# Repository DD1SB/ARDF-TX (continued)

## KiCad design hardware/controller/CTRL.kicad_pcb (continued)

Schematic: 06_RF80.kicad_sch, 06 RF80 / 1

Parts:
C40, C42, C43: 100n; C_0603_1608Metric_CTL; MPN CL10B104KB8NNNC
C41: 1u; C_0603_1608Metric_CTL; MPN CL10A105KB8NNNC
J4: RF80 keyed controller link; IDC16_61201621621; MPN 61201621621
R80, R101, R103, R105, R107: 10k; R_0603_1608Metric_CTL; MPN RC0603FR-0710KL
R100, R102, R104, R106, R108: 100; R_0603_1608Metric_CTL; MPN RC0603FR-07100RL
U40: TPS22918DBVR; SOT-23-6_CTL; MPN TPS22918DBVR
U41: SN74LVC244APWR; TSSOP-20_4.4x6.5mm_P0.65mm_CTL; MPN SN74LVC244APWR
U42: SN74LVC125APWR; TSSOP-14_4.4x5mm_P0.65mm_CTL; MPN SN74LVC125APWR

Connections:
ARM: U41.2 (2_A); also elsewhere on the board
FOX_REQ: U41.13 (13_A); also elsewhere on the board
GND: C40.2, C41.2, C42.2, C43.2, J4.2 (2_IO), J4.4 (4_IO), J4.16 (16_IO), R101.2, R103.2, R105.2, R107.2, U40.2 (2_GND), U41.10 (10_GND), U42.5 (5_A), U42.7 (7_GND), U42.9 (9_A), U42.12 (12_A); also elsewhere on the board
KEY: U41.4 (4_A); also elsewhere on the board
MUTE_RELEASE: U41.8 (8_A); also elsewhere on the board
OE80_N: R80.2, U41.1 (1_OE1_N), U41.19 (19_OE2_N), U42.1 (1_OE_N); also elsewhere on the board
PACK4_SOFT: U42.2 (2_A); also elsewhere on the board
PA_REQ: U41.11 (11_A); also elsewhere on the board
POWER80: U40.3 (3_ON); also elsewhere on the board
PROGRESS: U41.6 (6_A); also elsewhere on the board
PWR0: U41.15 (15_A); also elsewhere on the board
PWR1: U41.17 (17_A); also elsewhere on the board
RF80_ARM: J4.7 (7_IO), R100.2, R101.1
RF80_ARM_BUF: R100.1, U41.18 (18_Y)
RF80_CW_KEY: J4.8 (8_IO), R102.2, R103.1
RF80_CW_KEY_BUF: R102.1, U41.16 (16_Y)
RF80_FAULT_N: J4.14 (14_IO); also elsewhere on the board
RF80_FOX_REQ: J4.10 (10_IO); also elsewhere on the board
RF80_FOX_REQ_BUF: U41.7 (7_Y); also elsewhere on the board
RF80_LEASE: J4.6 (6_IO), R104.2, R105.1
RF80_LEASE_BUF: R104.1, U41.14 (14_Y)
RF80_MUTE_N: J4.13 (13_IO), R106.2, R107.1
RF80_MUTE_N_BUF: R106.1, U41.12 (12_Y)
RF80_PACK4_OK: J4.15 (15_IO); also elsewhere on the board
RF80_PACK4_OK_BUF: U42.3 (3_Y); also elsewhere on the board
RF80_PA_REQ: J4.9 (9_IO), R108.2; also elsewhere on the board
RF80_PA_REQ_BUF: R108.1, U41.9 (9_Y)
RF80_PWR0: J4.11 (11_IO); also elsewhere on the board
RF80_PWR0_BUF: U41.5 (5_Y); also elsewhere on the board
RF80_PWR1: J4.12 (12_IO); also elsewhere on the board
RF80_PWR1_BUF: U41.3 (3_Y); also elsewhere on the board
RF80_SCL: J4.3 (3_IO); also elsewhere on the board
RF80_SDA: J4.5 (5_IO); also elsewhere on the board
V3V3: U40.1 (1_IN); also elsewhere on the board
V3V3_RF80: C40.1, C41.1, C42.1, C43.1, J4.1 (1_IO), R80.1, U40.5 (5_QOD), U40.6 (6_OUT), U41.20 (20_VCC), U42.4 (4_OE_N), U42.10 (10_OE_N), U42.13 (13_OE_N), U42.14 (14_VCC); also elsewhere on the board

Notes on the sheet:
06 RF80 / 1
M6-C1R1 candidate: REVIEW / ALL hardware measurements NOT RUN / no ordering or manufacture.

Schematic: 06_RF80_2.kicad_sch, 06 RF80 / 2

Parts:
C44, C45: 100n; C_0603_1608Metric_CTL; MPN CL10B104KB8NNNC
R81: 2.2k; R_0603_1608Metric_CTL; MPN RC0603FR-072K2L
R109, R111, R113, R115, R117: 10k; R_0603_1608Metric_CTL; MPN RC0603FR-0710KL
R110, R112, R114, R116: 100; R_0603_1608Metric_CTL; MPN RC0603FR-07100RL
U43: TCA9517DR; SOIC-8_3.9x4.9mm_P1.27mm_CTL; MPN TCA9517DR

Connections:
BUS80_EN: U43.5 (5_EN); also elsewhere on the board
GND: C44.2, C45.2, R109.2, R111.2, R113.2, R115.2, R117.2, U43.4 (4_GND); also elsewhere on the board
RF80_FAULT_N: R81.1; also elsewhere on the board
RF80_FOX_REQ: R110.2, R111.1; also elsewhere on the board
RF80_FOX_REQ_BUF: R110.1; also elsewhere on the board
RF80_PACK4_OK: R116.2, R117.1; also elsewhere on the board
RF80_PACK4_OK_BUF: R116.1; also elsewhere on the board
RF80_PA_REQ: R109.1; also elsewhere on the board
RF80_PWR0: R112.2, R113.1; also elsewhere on the board
RF80_PWR0_BUF: R112.1; also elsewhere on the board
RF80_PWR1: R114.2, R115.1; also elsewhere on the board
RF80_PWR1_BUF: R114.1; also elsewhere on the board
RF80_SCL: U43.7 (7_SCLB); also elsewhere on the board
RF80_SDA: U43.6 (6_SDAB); also elsewhere on the board
RTC80_SCL: U43.2 (2_SCLA); also elsewhere on the board
RTC80_SDA: U43.3 (3_SDAA); also elsewhere on the board
V3V3: C45.1, U43.1 (1_VCCA); also elsewhere on the board
V3V3_RF80: C44.1, R81.2, U43.8 (8_VCCB); also elsewhere on the board

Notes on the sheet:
06 RF80 / 2
M6-C1R1 candidate: REVIEW / ALL hardware measurements NOT RUN / no ordering or manufacture.

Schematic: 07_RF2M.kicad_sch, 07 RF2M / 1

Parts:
C50, C52, C53: 100n; C_0603_1608Metric_CTL; MPN CL10B104KB8NNNC
C51: 1u; C_0603_1608Metric_CTL; MPN CL10A105KB8NNNC
J5: RF2M keyed controller link; IDC20_61202021621; MPN 61202021621
R90, R119, R121, R123, R125: 10k; R_0603_1608Metric_CTL; MPN RC0603FR-0710KL
R118, R120, R122, R124, R126: 100; R_0603_1608Metric_CTL; MPN RC0603FR-07100RL
U50: TPS22918DBVR; SOT-23-6_CTL; MPN TPS22918DBVR
U51: SN74LVC244APWR; TSSOP-20_4.4x6.5mm_P0.65mm_CTL; MPN SN74LVC244APWR
U52: SN74LVC125APWR; TSSOP-14_4.4x5mm_P0.65mm_CTL; MPN SN74LVC125APWR

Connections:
AF_PWM: U51.17 (17_A); also elsewhere on the board
ARM: U51.2 (2_A); also elsewhere on the board
GND: C50.2, C51.2, C52.2, C53.2, J5.2 (2_IO), J5.17 (17_IO), J5.18 (18_IO), R119.2, R121.2, R123.2, R125.2, U50.2 (2_GND), U51.10 (10_GND), U52.7 (7_GND), U52.12 (12_A); also elsewhere on the board
KEY: U51.6 (6_A); also elsewhere on the board
LEVEL_PWM: U52.2 (2_A); also elsewhere on the board
MUTE_RELEASE: U51.11 (11_A); also elsewhere on the board
OE2M_N: R90.2, U51.1 (1_OE1_N), U51.19 (19_OE2_N), U52.1 (1_OE_N), U52.4 (4_OE_N), U52.10 (10_OE_N); also elsewhere on the board
PATH_TRAIN: U51.13 (13_A); also elsewhere on the board
PA_PREPARE: U52.9 (9_A); also elsewhere on the board
POWER2M: U50.3 (3_ON); also elsewhere on the board
PREPARE: U52.5 (5_A); also elsewhere on the board
PROFILE_FULL: U51.15 (15_A); also elsewhere on the board
PROGRESS: U51.8 (8_A); also elsewhere on the board
RF2M_AF_PWM: J5.13 (13_IO); also elsewhere on the board
RF2M_AF_PWM_BUF: U51.3 (3_Y); also elsewhere on the board
RF2M_ARM: J5.5 (5_IO), R118.2, R119.1
RF2M_ARM_BUF: R118.1, U51.18 (18_Y)
RF2M_FAULT_N: J5.16 (16_IO); also elsewhere on the board
RF2M_I2C_SCL: J5.4 (4_IO); also elsewhere on the board
RF2M_I2C_SDA: J5.3 (3_IO); also elsewhere on the board
RF2M_KEY: J5.7 (7_IO), R122.2, R123.1
RF2M_KEY_BUF: R122.1, U51.14 (14_Y)
RF2M_LEVEL_PWM: J5.14 (14_IO); also elsewhere on the board
RF2M_LEVEL_PWM_BUF: U52.3 (3_Y); also elsewhere on the board
RF2M_MODULE_ID: J5.19 (19_IO); also elsewhere on the board
RF2M_MUTE_N: J5.9 (9_IO), R126.2; also elsewhere on the board
RF2M_MUTE_N_BUF: R126.1, U51.9 (9_Y)
RF2M_PATH_TRAIN: J5.11 (11_IO); also elsewhere on the board
RF2M_PATH_TRAIN_BUF: U51.7 (7_Y); also elsewhere on the board
RF2M_PA_PREPARE: J5.20 (20_IO); also elsewhere on the board
RF2M_PA_PREPARE_BUF: U52.8 (8_Y); also elsewhere on the board
RF2M_PA_RAIL_ADC: J5.10 (10_IO); also elsewhere on the board
RF2M_PREPARE: J5.15 (15_IO); also elsewhere on the board
RF2M_PREPARE_BUF: U52.6 (6_Y); also elsewhere on the board
RF2M_PROFILE_FULL: J5.12 (12_IO); also elsewhere on the board
RF2M_PROFILE_FULL_BUF: U51.5 (5_Y); also elsewhere on the board
RF2M_PROGRESS: J5.8 (8_IO), R124.2, R125.1
RF2M_PROGRESS_BUF: R124.1, U51.12 (12_Y)
RF2M_SLOT: J5.6 (6_IO), R120.2, R121.1
RF2M_SLOT_BUF: R120.1, U51.16 (16_Y)
SLOT: U51.4 (4_A); also elsewhere on the board
V3V3: U50.1 (1_IN); also elsewhere on the board
V3V3_RF2M: C50.1, C51.1, C52.1, C53.1, J5.1 (1_IO), R90.1, U50.5 (5_QOD), U50.6 (6_OUT), U51.20 (20_VCC), U52.13 (13_OE_N), U52.14 (14_VCC); also elsewhere on the board

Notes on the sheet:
07 RF2M / 1
M6-C1R1 candidate: REVIEW / ALL hardware measurements NOT RUN / no ordering or manufacture.

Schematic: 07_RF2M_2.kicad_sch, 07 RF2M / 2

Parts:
C54, C55: 100n; C_0603_1608Metric_CTL; MPN CL10B104KB8NNNC
R91, R127, R129, R131, R133, R135, R137, R139: 10k; R_0603_1608Metric_CTL; MPN RC0603FR-0710KL
R128, R130, R132, R134, R136, R138: 100; R_0603_1608Metric_CTL; MPN RC0603FR-07100RL
U53: TCA9517DR; SOIC-8_3.9x4.9mm_P1.27mm_CTL; MPN TCA9517DR

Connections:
BUS2M_EN: U53.5 (5_EN); also elsewhere on the board
GND: C54.2, C55.2, R91.2, R127.2, R129.2, R131.2, R133.2, R135.2, R137.2, R139.2, U53.4 (4_GND); also elsewhere on the board
RF2M_AF_PWM: R132.2, R133.1; also elsewhere on the board
RF2M_AF_PWM_BUF: R132.1; also elsewhere on the board
RF2M_FAULT_N: R91.1; also elsewhere on the board
RF2M_I2C_SCL: U53.7 (7_SCLB); also elsewhere on the board
RF2M_I2C_SDA: U53.6 (6_SDAB); also elsewhere on the board
RF2M_LEVEL_PWM: R134.2, R135.1; also elsewhere on the board
RF2M_LEVEL_PWM_BUF: R134.1; also elsewhere on the board
RF2M_MUTE_N: R127.1; also elsewhere on the board
RF2M_PATH_TRAIN: R128.2, R129.1; also elsewhere on the board
RF2M_PATH_TRAIN_BUF: R128.1; also elsewhere on the board
RF2M_PA_PREPARE: R138.2, R139.1; also elsewhere on the board
RF2M_PA_PREPARE_BUF: R138.1; also elsewhere on the board
RF2M_PREPARE: R136.2, R137.1; also elsewhere on the board
RF2M_PREPARE_BUF: R136.1; also elsewhere on the board
RF2M_PROFILE_FULL: R130.2, R131.1; also elsewhere on the board
RF2M_PROFILE_FULL_BUF: R130.1; also elsewhere on the board
RF2M_SCL: U53.2 (2_SCLA); also elsewhere on the board
RF2M_SDA: U53.3 (3_SDAA); also elsewhere on the board
V3V3: C55.1, U53.1 (1_VCCA); also elsewhere on the board
V3V3_RF2M: C54.1, U53.8 (8_VCCB); also elsewhere on the board

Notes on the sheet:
07 RF2M / 2
M6-C1R1 candidate: REVIEW / ALL hardware measurements NOT RUN / no ordering or manufacture.

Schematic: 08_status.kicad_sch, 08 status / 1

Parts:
C60: 100n; C_0603_1608Metric_CTL; MPN CL10B104KB8NNNC
R93: 10k; R_0603_1608Metric_CTL; MPN RC0603FR-0710KL
U60: SN74LVC2G17DCKR; SOT-363_SC-70-6_CTL; MPN SN74LVC2G17DCKR

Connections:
GND: C60.2, R93.2, U60.3 (3_GND); also elsewhere on the board
RF2M_FAULT: U60.2 (2_2Y); also elsewhere on the board
RF2M_FAULT_N: U60.4 (4_2A); also elsewhere on the board
RF80_FAULT: U60.5 (5_1Y); also elsewhere on the board
RF80_FAULT_N: R93.1, U60.1 (1_1A); also elsewhere on the board
V3V3: C60.1, U60.6 (6_VCC); also elsewhere on the board

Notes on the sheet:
08 status / 1
M6-C1R1 candidate: REVIEW / ALL hardware measurements NOT RUN / no ordering or manufacture.

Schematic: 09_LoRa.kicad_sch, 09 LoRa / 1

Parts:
C70: 100n; C_0603_1608Metric_CTL; MPN CL10B104KB8NNNC; not fitted
C71: 10u 10V; C_0603_1608Metric_CTL; MPN CL10A106KP8NNNC; not fitted
J7: LoRa antenna U.FL; UFL_Standard; MPN U.FL-R-SMT-1(10); not fitted
R70, R71: 10k; R_0603_1608Metric_CTL; MPN RC0603FR-0710KL; not fitted
U70: Silicontra SX1262TR8-GC; Silicontra_SX1262ZTR8_GC; MPN SX1262TR8-GC; not fitted

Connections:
GND: C70.2, C71.2, J7.2 (2_IO), U70.1 (1_IO), U70.2 (2_IO), U70.3 (3_IO), U70.4 (4_IO), U70.11 (11_IO), U70.12 (12_IO), U70.19 (19_IO), U70.20 (20_IO), U70.22 (22_IO); also elsewhere on the board
LORA_ANT: J7.1 (1_IO), U70.21 (21_IO)
LORA_BUSY: U70.10 (10_BUSY); also elsewhere on the board
LORA_DIO1: U70.5 (5_DIO1); also elsewhere on the board
LORA_NSS: R70.2, U70.17 (17_NSS); also elsewhere on the board
LORA_RESET: R71.2, U70.18 (18_RST_N); also elsewhere on the board
SPI_MISO: U70.15 (15_MISO); also elsewhere on the board
SPI_MOSI: U70.16 (16_MOSI); also elsewhere on the board
SPI_SCK: U70.14 (14_SCK); also elsewhere on the board
V3V3: C70.1, C71.1, R70.1, R71.1, U70.13 (13_VCC); also elsewhere on the board

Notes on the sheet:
09 LoRa / 1
M6-C1R1 candidate: REVIEW / ALL hardware measurements NOT RUN / no ordering or manufacture.

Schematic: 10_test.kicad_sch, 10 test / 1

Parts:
TP1: V3V3; TestPoint_Pad_D1.0mm_CTL; MPN PCB_FEATURE
TP2: GND; TestPoint_Pad_D1.0mm_CTL; MPN PCB_FEATURE
TP3: VIN_SYS; TestPoint_Pad_D1.0mm_CTL; MPN PCB_FEATURE
TP4: SAFE_OE_N; TestPoint_Pad_D1.0mm_CTL; MPN PCB_FEATURE

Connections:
GND: TP2.1; also elsewhere on the board
SAFE_OE_N: TP4.1; also elsewhere on the board
V3V3: TP1.1; also elsewhere on the board
VIN_SYS: TP3.1; also elsewhere on the board

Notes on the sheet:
10 test / 1
M6-C1R1 candidate: REVIEW / ALL hardware measurements NOT RUN / no ordering or manufacture.

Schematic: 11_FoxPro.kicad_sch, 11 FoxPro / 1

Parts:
J8: FOXPRO / G-D-V UNAVAILABLE; JST_PH_B3B-PH-K_1x03_P2.00mm_Vertical_L2; MPN B3B-PH-K-S(LF)(SN); not fitted
Q80: BSS138BK TX open-drain; SOT-23_CTL; MPN BSS138BK,215; not fitted
Q81: MMBT3904 hardware inhibit; SOT-23_CTL; MPN MMBT3904LT1G; not fitted
Q82: BSS138BK isolated-gate RX; SOT-23_CTL; MPN BSS138BK,215; not fitted
R300, R301: 0; R_0603_1608Metric_CTL; MPN RC0603JR-070RL
R302, R303: 0; R_0603_1608Metric_CTL; MPN RC0603JR-070RL; not fitted
R304: 680; R_2512_6332Metric_L2; MPN RC2512FK-07680RL; not fitted
R305, R307: 1k; R_0603_1608Metric_CTL; MPN RC0603FR-071KL; not fitted
R306, R308: 4.7k; R_0603_1608Metric_CTL; MPN RC0603FR-074K7L; not fitted
R309: 47k; R_0603_1608Metric_CTL; MPN RC0603FR-0747KL; not fitted
R310, R312: 100k; R_0603_1608Metric_CTL; MPN RC0603FR-07100KL; not fitted
R311: 160; R_0603_1608Metric_CTL; MPN RC0603FR-07160RL; not fitted
R314: 470; R_2512_6332Metric_L2; MPN RC2512FK-07470RL; not fitted

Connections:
FOX_DATA: J8.2 (2_IO), R304.1, R309.1, R312.1; also elsewhere on the board
FOX_EN_B: Q81.1 (1_IO), R305.2, R306.1
FOX_GND: J8.1 (1_IO), R314.1; also elsewhere on the board
FOX_RX: Q82.3 (D), R303.2, R311.2; also elsewhere on the board
FOX_RX_GATE: Q82.1 (G), R309.2, R310.1; also elsewhere on the board
FOX_SINK: Q80.3 (D), R304.2; also elsewhere on the board
FOX_TX: R302.2, R305.1
FOX_TX_B: Q80.1 (G), Q81.3 (3_IO), R307.2, R308.1; also elsewhere on the board
FOX_V_UNAVAILABLE: J8.3 (3_IO); also elsewhere on the board
GND: Q80.2 (S), Q81.2 (2_IO), Q82.2 (S), R306.2, R308.2, R310.2, R312.2, R314.2; also elsewhere on the board
REC_RX: R301.2; also elsewhere on the board
REC_TX: R300.2; also elsewhere on the board
SAFE: R307.1; also elsewhere on the board
UART_RX: R301.1, R303.1; also elsewhere on the board
UART_TX: R300.1, R302.1; also elsewhere on the board
V3V3: R311.1; also elsewhere on the board

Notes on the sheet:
11 FoxPro / 1
M6-L2 candidate: REVIEW / ALL hardware measurements NOT RUN / no ordering or manufacture.

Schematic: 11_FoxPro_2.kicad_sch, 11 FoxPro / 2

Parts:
C84: 10n; C_0603_1608Metric_CTL; MPN CL10B103KB8NNNC; not fitted
D80, D83, D84: PESD1IVN24-A bidirectional TVS; D_SOD-323_L2; MPN PESD1IVN24-AX; not fitted
D81: BAS316 negative collector clamp; D_SOD-323_L2; MPN BAS316,115; not fitted
D82: BZX84-C12 gate clamp; SOT-23_CTL; MPN BZX84-C12,215; not fitted
R313: 0; R_0603_1608Metric_CTL; MPN RC0603JR-070RL; not fitted
R315: 620; R_0603_1608Metric_CTL; MPN RC0603FR-07620RL; not fitted
R316: 470; R_2512_6332Metric_L2; MPN RC2512FK-07470RL; not fitted

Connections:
FOX_DATA: D80.1 (1_IO); also elsewhere on the board
FOX_GND: D84.1 (1_IO), R313.2, R316.1; also elsewhere on the board
FOX_RX: R315.1; also elsewhere on the board
FOX_RX_GATE: D82.3 (K); also elsewhere on the board
FOX_SINK: D81.1 (1_K); also elsewhere on the board
FOX_TX_B: C84.1; also elsewhere on the board
FOX_V_UNAVAILABLE: D83.1 (1_IO), R313.1; also elsewhere on the board
GND: C84.2, D80.2 (2_IO), D81.2 (2_IO), D82.1 (A), D83.2 (2_IO), D84.2 (2_IO), R315.2, R316.2; also elsewhere on the board

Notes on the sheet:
11 FoxPro / 2
M6-L2 candidate: REVIEW / ALL hardware measurements NOT RUN / no ordering or manufacture.

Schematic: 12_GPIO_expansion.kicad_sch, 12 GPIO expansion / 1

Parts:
C80, C81, C82, C83: 100n; C_0603_1608Metric_CTL; MPN CL10B104KB8NNNC; not fitted
J9: GPIO / 3V3 ONLY / 10mA; PinHeader_2x05_P2.54mm_Vertical_L2; MPN 61301021121; not fitted
R320, R321: 4.7k; R_0603_1608Metric_CTL; MPN RC0603FR-074K7L; not fitted
R322, R323, R324, R325, R326, R327, R328, R329: 1k; R_0603_1608Metric_CTL; MPN RC0603FR-071KL; not fitted
R330: 22; R_2512_6332Metric_L2; MPN RC2512FK-0722RL; not fitted
R331: 10k; R_0603_1608Metric_CTL; MPN RC0603FR-0710KL; not fitted
U80: TCA9534APWR / 0x38; TSSOP-16_4.4x5mm_P0.65mm_CTL; MPN TCA9534APWR; not fitted
U81: TCA9517DR optional bus buffer; SOIC-8_3.9x4.9mm_P1.27mm_CTL; MPN TCA9517DR; not fitted
U82: LM66100DCKR reverse block; SOT-363_SC-70-6_CTL; MPN LM66100DCKR; not fitted

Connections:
EXP_P0: R322.1, U80.4 (4_P0)
EXP_P1: R323.1, U80.5 (5_P1)
EXP_P2: R324.1, U80.6 (6_P2)
EXP_P3: R325.1, U80.7 (7_P3)
EXP_P4: R326.1, U80.9 (9_P4)
EXP_P5: R327.1, U80.10 (10_P5)
EXP_P6: R328.1, U80.11 (11_P6)
EXP_P7: R329.1, U80.12 (12_P7)
EXP_SCL: R321.2, U80.14 (14_SCL), U81.7 (7_IO)
EXP_SDA: R320.2, U80.15 (15_SDA), U81.6 (6_IO)
EXP_VDD: C80.1, C82.1, R320.1, R321.1, R330.1, U80.16 (16_VCC), U81.5 (5_IO), U81.8 (8_IO), U82.3 (CE), U82.6 (VOUT)
GND: C80.2, C81.2, C82.2, C83.2, J9.10 (10_IO), R331.2, U80.1 (1_A0), U80.2 (2_A1), U80.3 (3_A2), U80.8 (8_GND), U81.4 (4_IO), U82.2 (GND), U82.5 (ST); also elsewhere on the board
HDR_3V3: J9.9 (9_IO), R330.2
HDR_P0: J9.1 (1_IO), R322.2
HDR_P1: J9.2 (2_IO), R323.2
HDR_P2: J9.3 (3_IO), R324.2
HDR_P3: J9.4 (4_IO), R325.2
HDR_P4: J9.5 (5_IO), R326.2
HDR_P5: J9.6 (6_IO), R327.2
HDR_P6: J9.7 (7_IO), R328.2
HDR_P7: J9.8 (8_IO), R329.2
RTC80_SCL: U81.2 (2_IO); also elsewhere on the board
RTC80_SDA: U81.3 (3_IO); also elsewhere on the board
V3V3: C81.1, C83.1, R331.1, U81.1 (1_IO), U82.1 (VIN); also elsewhere on the board

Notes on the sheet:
12 GPIO expansion / 1
M6-L2 candidate: REVIEW / ALL hardware measurements NOT RUN / no ordering or manufacture.

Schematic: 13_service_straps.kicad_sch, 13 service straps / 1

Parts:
JP1: GPIO3 SERVICE ONLY / OPEN; SolderJumper-2_P1.3mm_Open_Pad1.0x1.5mm_L2; MPN PCB solder bridge (no purchased part); not fitted
JP3: GPIO46 SERVICE ONLY / OPEN; SolderJumper-2_P1.3mm_Open_Pad1.0x1.5mm_L2; MPN PCB solder bridge (no purchased part); not fitted
TP81: GPIO3 AFTER OPEN LINK; TestPoint_Pad_D1.0mm_CTL; MPN PCB pad (no purchased part); not fitted
TP83: GPIO46 AFTER OPEN LINK; TestPoint_Pad_D1.0mm_CTL; MPN PCB pad (no purchased part); not fitted

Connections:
ACCESS3: JP1.2 (2_IO), TP81.1
ACCESS46: JP3.2 (2_IO), TP83.1
STRAP3: JP1.1 (1_IO); also elsewhere on the board
STRAP46: JP3.1 (1_IO); also elsewhere on the board

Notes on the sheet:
13 service straps / 1
M6-L2 candidate: REVIEW / ALL hardware measurements NOT RUN / no ordering or manufacture.

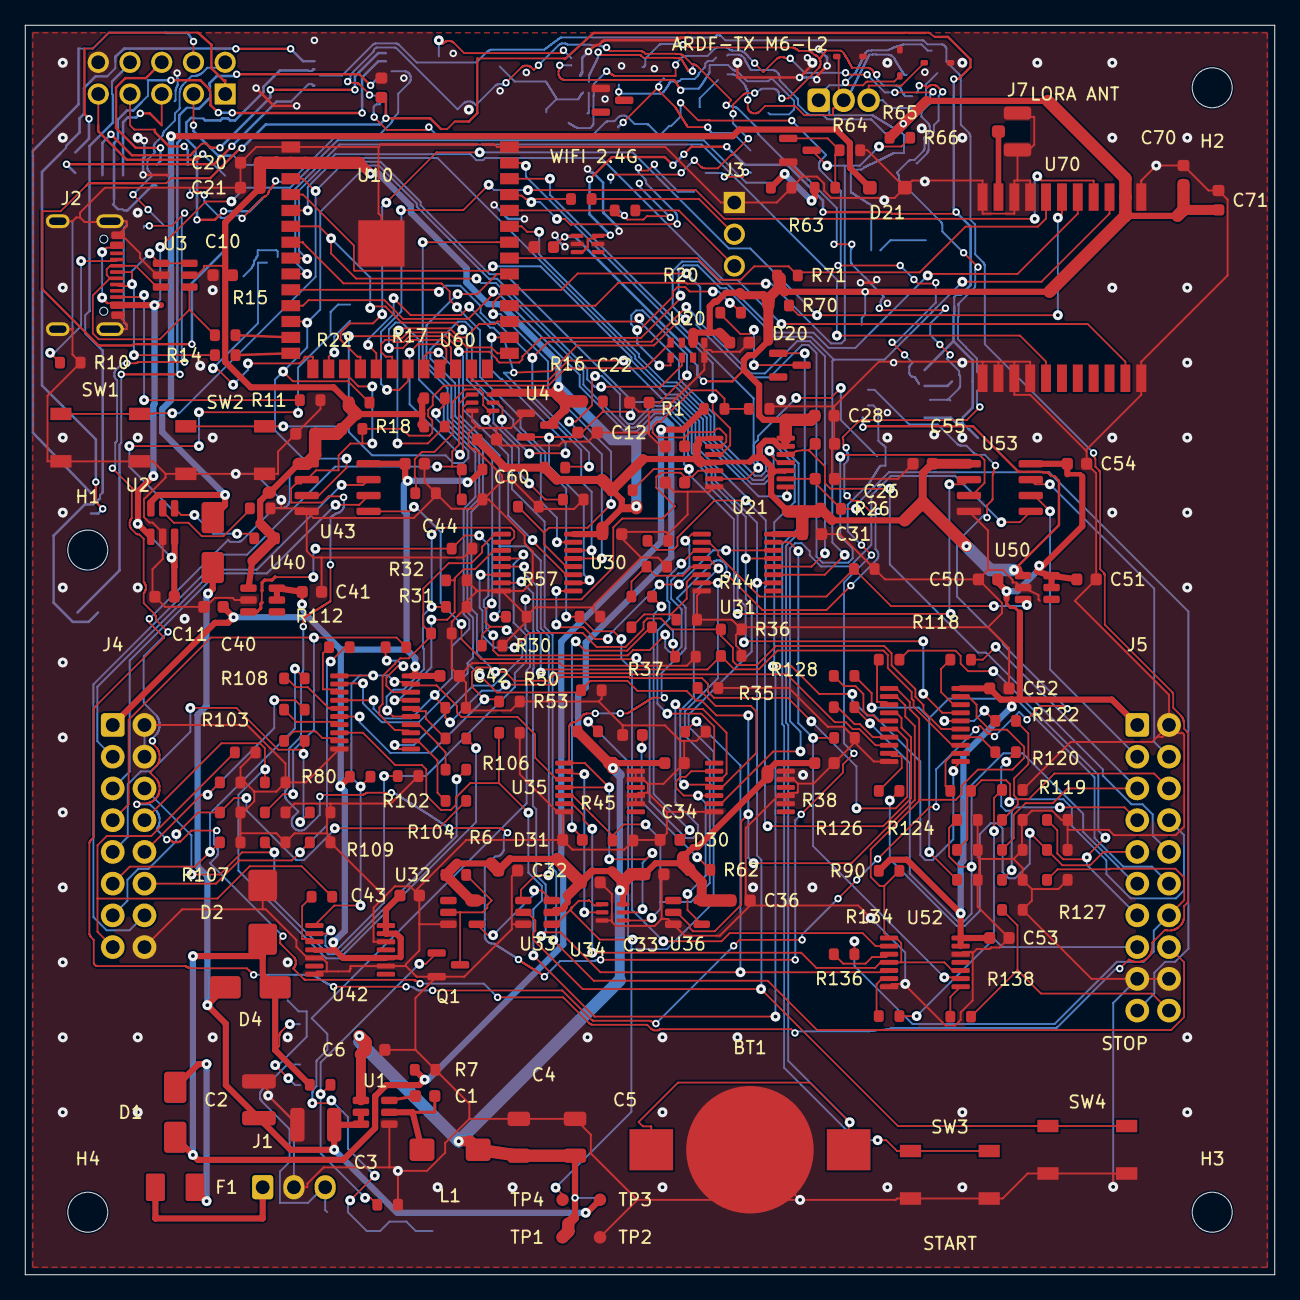
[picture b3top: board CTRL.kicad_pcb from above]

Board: 2 copper layers, 100.0 x 100.0 mm, 256 parts (48 on the bottom side), 175 nets.

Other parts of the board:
H1, H2, H3, H4: MountingHole_3.2mm_M3; MountingHole_3.2mm_M3_CTL

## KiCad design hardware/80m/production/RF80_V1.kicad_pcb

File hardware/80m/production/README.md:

# RF80 V1R1 — standard prototype manufacturing candidate

Open **RF80_V1.kicad_pro** here. The active M4A-V1R1 is a **150 × 110 mm**, two-layer, 1.6 mm / 1 oz standard FR4 candidate with lead-free HASL. It preserves the Si5351–LM5134B–IRF610/BD140 circuit, independent Fox path and controller/protection contracts. The changes concern local THT landings, legend and manufacturing settings.

- [Current engineering decision](../../../docs/M4A_V1R1_REVIEW_DECISION.md)
- [Current review and five-board package](review/M4A-V1R1/README.md)
- [Ordinary finished-hole audit](../../../docs/M4A_V1R1_HOLE_AND_FOOTPRINT_AUDIT.md)
- [Proposed first-evaluation transition](../../../docs/M4A_V1R1_PROTOTYPE_TRANSITION.md)
- Preserved [original M4A-V1 review](review/M4A-V1/README.md) and [original decision](../../../docs/M4A_REVIEW_DECISION.md), baseline 4d2f592. Frozen E2 at 1245023 / m3b-e2 remains unchanged one directory above.

**GO for independent bare-PCB manufacturing review.** The old E2-first restriction remains historical evidence: the V1R1-first proposal requires user review before upload/fabrication approval. No accepted ADR or historical evidence changed. Physical fit, power, protection, RF, thermal, spectrum and endurance tests are all **NOT_RUN**.

FULL and FOX_ONLY are explicit populations of the same PCB. Full omits R228/R348/R349; Fox fits these links and omits the normal PA. Full includes the off-board insulated TH301 sensor. Use current population/placement records for Fox assembly. No acceptance tag, order, upload, assembly, power-up or RF is authorized.

Do not run old derivation/placement scripts on the candidate. They recreate obsolete routing input. Use the dedicated `m4a_v1r1` wrapper and current reproduction instructions; historical exporters would overwrite preserved review data. [Licence and attribution](LICENSES.md).

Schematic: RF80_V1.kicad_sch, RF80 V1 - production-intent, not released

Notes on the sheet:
Classic 3 W / 1.2 W; Sprint calibrated; independent Fox 10 mW NORMAL: protected 4S, 12.0-16.8 V. FOX-only: controller 3.3 V from 2S. No 2 m changes. PRODUCTION-INTENT - NOT RELEASED. No measured prototype results. Inter-sheet connections use explicit named global nets. Read docs/M4A_REVIEW_DECISION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

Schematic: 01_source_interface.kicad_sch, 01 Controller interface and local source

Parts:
C101, C102: 100n; C_0603_1608Metric; MPN CC0603KRX7R8BB104
C103: 1u; C_0805_2012Metric; MPN CC0805KKX7R9BB105
J101: IDC16 controller; Wurth_61201621621; MPN Wurth 61201621621
R101, R102: 4.7k; R_0603_1608Metric; MPN RC0603FR-074K7L
R103: 100k; R_0603_1608Metric; MPN RC0603FR-07100KL
R110, R111, R112, R113, R114, R115, R116, R117, R118: 47k; R_0603_1608Metric; MPN RC0603FR-0747KL
TP101: V3V3; TestPoint_Pad_D1.0mm; MPN PCB pad / no purchased component
TP102: CLK_PA; TestPoint_Pad_D1.0mm; MPN PCB pad / no purchased component
TP103: CLK_FOX; TestPoint_Pad_D1.0mm; MPN PCB pad / no purchased component
TP105: GND; TestPoint_Pad_D1.0mm; MPN PCB pad / no purchased component
U101: SI5351A-B-GT; MSOP-10_3x3mm_P0.5mm; MPN SI5351A-B-GT
Y101: 25 MHz / CL10 pF; Crystal_SMD_5032-4Pin_5.0x3.2mm; MPN ABM3B-25.000MHZ-10-1-U-T

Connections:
ARM: J101.7, R111.1; also elsewhere on the board
CLK_FOX: TP103.1, U101.6 (CLK2); also elsewhere on the board
CLK_PA: TP102.1, U101.10 (CLK0); also elsewhere on the board
CW_KEY: J101.8, R112.1; also elsewhere on the board
FAULT_N: J101.14, R103.2; also elsewhere on the board
FOX_REQ: J101.10, R114.1; also elsewhere on the board
GND: C101.2, C102.2, C103.2, J101.2, J101.4, J101.16, R110.2, R111.2, R112.2, R113.2, R114.2, R115.2, R116.2, R117.2, R118.2, TP105.1, U101.8 (GND), Y101.2 (G), Y101.4 (G); also elsewhere on the board
LEASE: J101.6, R110.1; also elsewhere on the board
MUTE_N: J101.13, R117.1; also elsewhere on the board
PACK4_OK: J101.15, R118.1; also elsewhere on the board
PA_REQ: J101.9, R113.1; also elsewhere on the board
PWR0: J101.11, R115.1; also elsewhere on the board
PWR1: J101.12, R116.1; also elsewhere on the board
SCL: J101.3, R101.2, U101.4 (SCL); also elsewhere on the board
SDA: J101.5, R102.2, U101.5 (SDA); also elsewhere on the board
V3V3: C101.1, C102.1, C103.1, J101.1, R101.1, R102.1, R103.1, TP101.1, U101.1 (VDD), U101.7 (VDDO); also elsewhere on the board
XA: U101.2 (XA), Y101.1
XB: U101.3 (XB), Y101.3

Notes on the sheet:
01 Controller interface and local source
One local Si5351; no MCU/RTC/UI on RF PCB. Shared 3.3 V stays powered during inhibited I2C setup. Controller wide-input regulator remains a proposal: evaluation fixture supplies bounded 3.3 V separately.
Logical contract: 3.3 V only; V3V3 3.135-3.465 V, absolute connector maximum 3.6 V. RoutePAcurrentthroughdedicatedJ301return; checkcontrollerground-harnesscurrent. PA raw power has separate J301 and return. LEASE 20 Hz software-progress toggles; ARM low before changing frequency, path or power. Any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
M4A-V1: PRODUCTION-INTENT - NOT RELEASED / all physical gates NOT_RUN.

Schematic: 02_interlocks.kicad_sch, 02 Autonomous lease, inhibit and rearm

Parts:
C201: 1u; C_0805_2012Metric; MPN CC0805KKX7R9BB105
C202, C203, C210, C211, C212: 100n; C_0603_1608Metric; MPN CC0603KRX7R8BB104
D201, D202: BAT54WS-7-F; D_SOD-323; MPN BAT54WS-7-F
Q201: BSS138BK,215; SOT-23; MPN BSS138BK,215
R201: 330k; R_0603_1608Metric; MPN RC0603FR-07330KL
R202, R203: 47k; R_0603_1608Metric; MPN RC0603FR-0747KL
U201: MCP100T-300I/TT; SOT-23; MPN MCP100T-300I/TT
U202: 74HC123D,653; SOIC-16_3.9x9.9mm_P1.27mm; MPN 74HC123D,653
U203: 74HC14D,653; SOIC-14_3.9x8.7mm_P1.27mm; MPN 74HC14D,653

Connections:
ARM: R203.1; also elsewhere on the board
ARM_CLK: U203.4; also elsewhere on the board
ARM_DELAY_N: U203.2, U203.3
ARM_RC: C203.1, R203.2, U203.1
BUS_HOLDOFF_N: U202.12 (~Q); also elsewhere on the board
BUS_RC: C202.1, D202.2 (A), R202.2, U202.7 (RCext)
CW_KEY: U203.11; also elsewhere on the board
FAULT_N: Q201.3 (D); also elsewhere on the board
FOX_REQ: U203.9; also elsewhere on the board
FOX_REQ_N: U203.8; also elsewhere on the board
GND: C201.2, C202.2, C203.2, C210.2, C211.2, C212.2, Q201.2 (S), U201.3 (VSS), U202.6 (Cext), U202.8 (GND), U202.9 (A), U202.14 (Cext), U203.7 (GND); also elsewhere on the board
KEY_N: U203.10; also elsewhere on the board
KEY_TAIL_C: U203.13; also elsewhere on the board
KEY_TAIL_N: U203.12; also elsewhere on the board
LEASE: U202.2 (B); also elsewhere on the board
LEASE_OK: U202.13 (Q); also elsewhere on the board
LEASE_RC: C201.1, D201.2 (A), R201.2, U202.15 (RCext)
LEASE_SEEN_N: U202.1 (A); also elsewhere on the board
NOT_ARMED: Q201.1 (G); also elsewhere on the board
PA_REQ: U203.5; also elsewhere on the board
PA_REQ_N: U203.6; also elsewhere on the board
POR_N: U201.1 (RESET_N), U202.3 (Clr), U202.11 (Clr); also elsewhere on the board
SCL: U202.10 (B); also elsewhere on the board
V3V3: C210.1, C211.1, C212.1, D201.1 (K), D202.1 (K), R201.1, R202.1, U201.2 (VDD), U202.16 (VCC), U203.14 (VCC); also elsewhere on the board

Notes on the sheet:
02 Autonomous lease, inhibit and rearm
Healthy-only asynchronous reset. Latched fault cannot recover while ARM remains high. ARM RC/Schmitt delay releases CLR before clocking. Requests exclusive; both asserted trips.
U202: first Q=pin13, /A=LEASE_SEEN_N; first validLEASE edge witnesses progress. Second /Q=pin12, /A=0,B=SCL. No blind ISR heartbeat: controller advances LEASE only after schedule and bus-state checks. Local mute is independent of firmware; hardware does not verify the requested frequency value. Nor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
M4A-V1: PRODUCTION-INTENT - NOT RELEASED / all physical gates NOT_RUN.

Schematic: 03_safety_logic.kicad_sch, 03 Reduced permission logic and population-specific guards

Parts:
C220, C222: 100n; C_0603_1608Metric; MPN CC0603KRX7R8BB104
D219, D220, D221, D222, D223, D224: BAT54WS-7-F; D_SOD-323; MPN BAT54WS-7-F
R219, R220: 2.2k; R_0603_1608Metric; MPN RC0603FR-072K2L
R225: 10k; R_0603_1608Metric; MPN RC0603FR-0710KL
R228: 0; R_0603_1608Metric; MPN RC0603JR-070RL; not fitted
U211: 74HC21D,653; SOIC-14_3.9x8.7mm_P1.27mm; MPN 74HC21D,653
U212: 74HC00D,653; SOIC-14_3.9x8.7mm_P1.27mm; MPN 74HC00D,653

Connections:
BUS_QUIET: U211.4; also elsewhere on the board
CORE_OK: U211.6, U211.9
EXCLUSIVE_OK: U211.10, U212.3
FOX_ID: D222.1 (K); also elsewhere on the board
FOX_MUTE: U212.11; also elsewhere on the board
FOX_PERMIT: U212.12; also elsewhere on the board
FOX_REQ: U212.2; also elsewhere on the board
GND: C220.2, C222.2, R225.2, R228.2, U211.7 (GND), U212.7 (GND); also elsewhere on the board
HEALTH_N: D220.2 (A), R219.2; also elsewhere on the board
KEY_TAIL: U212.8, U212.13; also elsewhere on the board
KEY_TAIL_N: U212.9, U212.10; also elsewhere on the board
LEASE_OK: U211.2; also elsewhere on the board
MODE_OK: U211.12, U212.6
MUTE_N: U211.5; also elsewhere on the board
PACK4_OK: D221.1 (K); also elsewhere on the board
PA_CONDITION_OK: D223.1 (K), D224.1 (K), R225.1, U211.13
PA_GUARD_RAW: D221.2 (A), D222.2 (A), D224.2 (A), R228.1; also elsewhere on the board
PA_REQ: U212.1; also elsewhere on the board
PA_REQ_N: D223.2 (A); also elsewhere on the board
POR_N: D219.1 (K); also elsewhere on the board
PWR0: U212.4; also elsewhere on the board
PWR1: U212.5; also elsewhere on the board
SAFE_RAW: D220.1 (K), U211.8
UV_POR_N: D219.2 (A), R220.2, U211.1; also elsewhere on the board
V3V3: C220.1, C222.1, R219.1, R220.1, U211.14 (VCC), U212.14 (VCC); also elsewhere on the board

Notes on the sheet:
03 Reduced permission logic and population-specific guards
Four redundant gate stages are replaced by one core tree and wired open-collector PA trips. Schottky logic margins and source loading remain E1 bench gates; no CMOS outputs are tied together.
M4A-V1: PRODUCTION-INTENT - NOT RELEASED / all physical gates NOT_RUN.

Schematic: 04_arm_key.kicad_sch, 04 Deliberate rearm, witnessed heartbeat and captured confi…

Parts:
C230, C231, C232, C233: 100n; C_0603_1608Metric; MPN CC0603KRX7R8BB104
Q225, Q226, Q227, Q228, Q229: BSS138BK,215; SOT-23; MPN BSS138BK,215
U221: 74HC11D,653; SOIC-14_3.9x8.7mm_P1.27mm; MPN 74HC11D,653
U222: 74HC08D,653; SOIC-14_3.9x8.7mm_P1.27mm; MPN 74HC08D,653
U223: 74HC74D,653; SOIC-14_3.9x8.7mm_P1.27mm; MPN 74HC74D,653
U224: 74HC174D,653; SOIC-16_3.9x9.9mm_P1.27mm; MPN 74HC174D,653

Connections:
ARM: U222.2, U224.9 (Cp); also elsewhere on the board
ARMED: U221.3, U221.9, U223.5 (Q); also elsewhere on the board
ARM_ACCEPT: Q229.1 (G), U221.5, U221.11, U223.2 (D), U224.12 (Q4)
ARM_CLK: U223.3 (C); also elsewhere on the board
BUS_HOLDOFF_N: U221.2; also elsewhere on the board
BUS_LINES_HIGH: U221.13, U222.11
BUS_QUIET: U221.12; also elsewhere on the board
CW_KEY: U222.5, U222.10; also elsewhere on the board
DROP_RETURN: Q226.2 (S), Q228.2 (S), Q229.3 (D)
FOX_DROP_MID: Q227.2 (S), Q228.3 (D)
FOX_KEY: U222.8; also elsewhere on the board
FOX_PERMIT: U221.8, U222.9; also elsewhere on the board
FOX_REQ: U224.11 (D3); also elsewhere on the board
FOX_REQ_N: Q228.1 (G); also elsewhere on the board
GND: C230.2, C231.2, C232.2, C233.2, Q229.2 (S), U221.7 (GND), U222.7 (GND), U223.7 (GND), U224.8 (GND), U224.14 (D5); also elsewhere on the board
HEALTH_N: Q225.3 (D), Q227.3 (D), U222.1, U224.1 (~Mr); also elsewhere on the board
KEY_N: U224.13 (D4); also elsewhere on the board
LEASE: U223.11 (C); also elsewhere on the board
LEASE_SEEN_N: U223.8 (~Q); also elsewhere on the board
NOT_ARMED: U223.6 (~Q); also elsewhere on the board
PATH_FOX: Q227.1 (G), U221.10, U224.10 (Q3)
PATH_PA: Q225.1 (G), U221.4, U224.7 (Q2)
PA_DROP_MID: Q225.2 (S), Q226.3 (D)
PA_KEY: U222.6; also elsewhere on the board
PA_PERMIT: U221.6, U222.4; also elsewhere on the board
PA_REQ: U224.6 (D2); also elsewhere on the board
PA_REQ_N: Q226.1 (G); also elsewhere on the board
POR_N: U221.1, U223.13 (~R); also elsewhere on the board
PWR0: U224.3 (D0); also elsewhere on the board
PWR1: U224.4 (D1); also elsewhere on the board
RESET_N: U222.3, U223.1 (~R); also elsewhere on the board
SCL: U222.12; also elsewhere on the board
SDA: U222.13; also elsewhere on the board
SEL_EXT: U224.2 (Q0); also elsewhere on the board
SEL_FULL: U224.5 (Q1); also elsewhere on the board
V3V3: C230.1, C231.1, C232.1, C233.1, U221.14 (VCC), U222.14 (VCC), U223.4 (~S), U223.10 (~S), U223.12 (D), U223.14 (VCC), U224.16 (VCC); also elsewhere on the board

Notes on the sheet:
04 Deliberate rearm, witnessed heartbeat and captured configuration
U224 captures path/mode/key-low on raw ARM; any health fault clears acceptance. U223 delayed clock can only arm an accepted context. A fault in the pending delay cannot rearm. Withdraw selected request: health clears context and RF permits. New raw ARM edge required. Fresh ARM low>=20ms, configure 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
M4A-V1: PRODUCTION-INTENT - NOT RELEASED / all physical gates NOT_RUN.

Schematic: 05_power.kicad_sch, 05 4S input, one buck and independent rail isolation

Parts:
C301, C302: 10u35; C_1210_3225Metric; MPN C3225X7R1V106M250AC
C303: 100n; C_0603_1608Metric; MPN CC0603KRX7R8BB104
C304, C305: 22u25; C_1210_3225Metric; MPN GRM32ER71E226KE15L
C306: 4.7n; C_0603_1608Metric; MPN CC0603JRNPO9BN472
D301: SS34; D_SMC; MPN SS34-E3/57T
D302: SMBJ17A TVS; D_SMB; MPN SMBJ17A
F301: 1.5 A fast / 32V; Fuse_467_0603; MPN Littelfuse 046701.5NR
J301: RAW protected pack; JST_VH_B2P_StandardPTH; MPN B2P-VH(LF)(SN)
L301: 10 uH >=3 A; SRP7050TA; MPN SRP7050TA-100M
Q301, Q302: BSS138BK,215; SOT-23; MPN BSS138BK,215
R301, R307: 47k; R_0603_1608Metric; MPN RC0603FR-0747KL
R302: 137k; R_0603_1608Metric; MPN RC0603FR-07137KL
R303: 20k; R_0603_1608Metric; MPN RC0603FR-0720KL
R304: 91k; R_0603_1608Metric; MPN RC0603FR-0791KL
R305: 24.9k; R_0603_1608Metric; MPN RC0603FR-0724K9L
R306: 100; R_0603_1608Metric; MPN RC0603FR-07100RL
U301: TPS54302DDCT; TSOT-23-6; MPN TPS54302DDCT
U302: TPS22810DBVR; SOT-23-6; MPN TPS22810DBVR

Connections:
BOOT_PA: C303.1, U301.6 (BOOT)
CT_PA: C306.1, U302.4 (CT)
FB_EXT: Q301.3 (D), R304.2
FB_FULL: Q302.3 (D), R305.2
FB_PA: R302.2, R303.1, R304.1, R305.1, U301.4 (FB)
GND: C301.2, C302.2, C304.2, C305.2, C306.2, D302.2 (A), J301.2, Q301.2 (S), Q302.2 (S), R301.2, R303.2, R307.2, U301.1 (GND), U302.2 (GND); also elsewhere on the board
PA_PERMIT: R301.1, R307.1, U301.5 (EN), U302.3 (EN/UVLO); also elsewhere on the board
QOD_PA: R306.1, U302.5 (QOD)
SEL_EXT: Q301.1 (G); also elsewhere on the board
SEL_FULL: Q302.1 (G); also elsewhere on the board
SW_PA: C303.2, L301.1, U301.2 (SW)
VBAT: F301.1, J301.1
VBAT_FUSED: D301.2 (A), F301.2
VIN_PA: C301.1, C302.1, D302.1 (K), U301.3 (VIN); also elsewhere on the board
VIN_PACK: D301.1 (K); also elsewhere on the board
VPA: C304.1, C305.1, L301.2, R302.1, U302.1 (VIN); also elsewhere on the board
VPA_ISO: R306.2, U302.6 (VOUT); also elsewhere on the board

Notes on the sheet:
05 4S input, one buck and independent rail isolation
Shared J301/F301/D301 input barrier; converter/loadswitch NORMAL only. Protected4S:12.0-16.8V. Fox-only retains input barrier/sense bypass, omits buck/loadswitch and watt-rail parts;2S powerscontroller+input sense. TPS22810 VIN must stay<=18V, including failed-buck transients;20V is absolute maximu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
M4A-V1: PRODUCTION-INTENT - NOT RELEASED / all physical gates NOT_RUN.

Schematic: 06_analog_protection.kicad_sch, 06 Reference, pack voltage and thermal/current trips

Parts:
C310, C313: 100n; C_0603_1608Metric; MPN CC0603KRX7R8BB104
C311: 10n; C_0603_1608Metric; MPN CC0603KRX7R9BB103
C314: 100n; C_0603_1608Metric; MPN CC0603KRX7R9BB104
R310: 180; R_0603_1608Metric; MPN RC0603FR-07180RL
R311: 1.5k; R_0603_1608Metric; MPN RC0603FR-071K5L
R312: 1k; R_0603_1608Metric; MPN RC0603FR-071KL
R313, R324: 309k; R_0603_1608Metric; MPN RC0603FR-07309KL
R314, R325: 10k; R_0603_1608Metric; MPN RC0603FR-0710KL
R321: 2.2k; R_0603_1608Metric; MPN RC0603FR-072K2L
U311: TL431AIDBZR; SOT-23; MPN TL431AIDBZR
U312: LM339BIDR; SOIC-14_3.9x8.7mm_P1.27mm; MPN LM339BIDR

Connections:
GND: C310.2, C311.2, C313.2, C314.2, R312.2, R314.2, R325.2, U311.3 (A), U312.12 (V-); also elsewhere on the board
I_PA_FILTER: U312.8 (-); also elsewhere on the board
PACK_4S_REF: U312.6 (-); also elsewhere on the board
PA_GUARD_RAW: R321.2, U312.1, U312.2, U312.13, U312.14; also elsewhere on the board
PA_OC_REF: U312.9 (+); also elsewhere on the board
PA_OV_REF: U312.11 (+); also elsewhere on the board
TEMP_HOT_REF: U312.4 (-); also elsewhere on the board
TEMP_SENSE: U312.5 (+); also elsewhere on the board
V3V3: C313.1, R310.1, R321.1, U312.3 (V+); also elsewhere on the board
VIN_PACK: C314.1, R313.1; also elsewhere on the board
VPA: R324.1; also elsewhere on the board
VREF_2V5: R310.2, R311.1, U311.1 (K), U311.2 (REF); also elsewhere on the board
VREF_TH: C310.1, R311.2, R312.1; also elsewhere on the board
V_PACK_SCALED: C311.1, R313.2, R314.1, U312.7 (+); also elsewhere on the board
V_PA_OV: R324.2, R325.1, U312.10 (-)

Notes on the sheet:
06 Reference, pack voltage and thermal/current trips
Real electrical trips; no RF power detector or continuous telemetry. Comparator inputs stay below1.5V. Shared reverse-protected J301 pack input retained for Fox-only; all PA converter/driver/final components DNP.
Nominal backup: commonUV5.810V/4Sbackup11.070V postreversebarrier; railOV8.973V. Controller operational endpoint remains6.0/12.0V with hysteresis; cell-group BMS external. Local pack sensing does not prove weakest-cell voltage. Hysteresis implemented by fault latch; rearm only after input exceeds q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
M4A-V1: PRODUCTION-INTENT - NOT RELEASED / all physical gates NOT_RUN.

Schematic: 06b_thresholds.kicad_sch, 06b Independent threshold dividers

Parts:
C312: 10n; C_0603_1608Metric; MPN CC0603KRX7R9BB103
R315: 127k; R_0603_1608Metric; MPN RC0603FR-07127KL
R316, R318, R327, R329: 10k; R_0603_1608Metric; MPN RC0603FR-0710KL
R317: 61.9k; R_0603_1608Metric; MPN RC0603FR-0761K9L
R326: 78.7k; R_0603_1608Metric; MPN RC0603FR-0778K7L
R328: 69.8k; R_0603_1608Metric; MPN RC0603FR-0769K8L

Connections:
GND: C312.2, R316.2, R318.2, R327.2, R329.2; also elsewhere on the board
PACK_2S_REF: C312.1, R315.2, R316.1; also elsewhere on the board
PACK_4S_REF: R317.2, R318.1; also elsewhere on the board
PA_OC_REF: R328.2, R329.1; also elsewhere on the board
PA_OV_REF: R326.2, R327.1; also elsewhere on the board
VREF_2V5: R315.1, R317.1, R326.1, R328.1; also elsewhere on the board

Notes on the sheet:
06b Independent threshold dividers
Independent reference dividers from regulated TL431 node, not a loaded shared half-reference. Pack and PA voltage signals divideby31.9; INA current signal divides by4. No comparator pin exceeds1.05V for28V input/rail or3.465V current-sense saturation. Thermal divider ratios sharetheir own<1.0V node.
Calculated at2.495V reference: commonUV5.810V protectedinput;4Sbackup11.070V protectedinput; OV8.973V rail; currenttrip1.251A. AddmeasuredSS34drop forrawpackthreshold. Controller operation stillstopsatapproximately6.0/12.0V; cell-group BMSexternal. Referencebias180ohm supports>=1mA TL431cathodecurr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
M4A-V1: PRODUCTION-INTENT - NOT RELEASED / all physical gates NOT_RUN.
